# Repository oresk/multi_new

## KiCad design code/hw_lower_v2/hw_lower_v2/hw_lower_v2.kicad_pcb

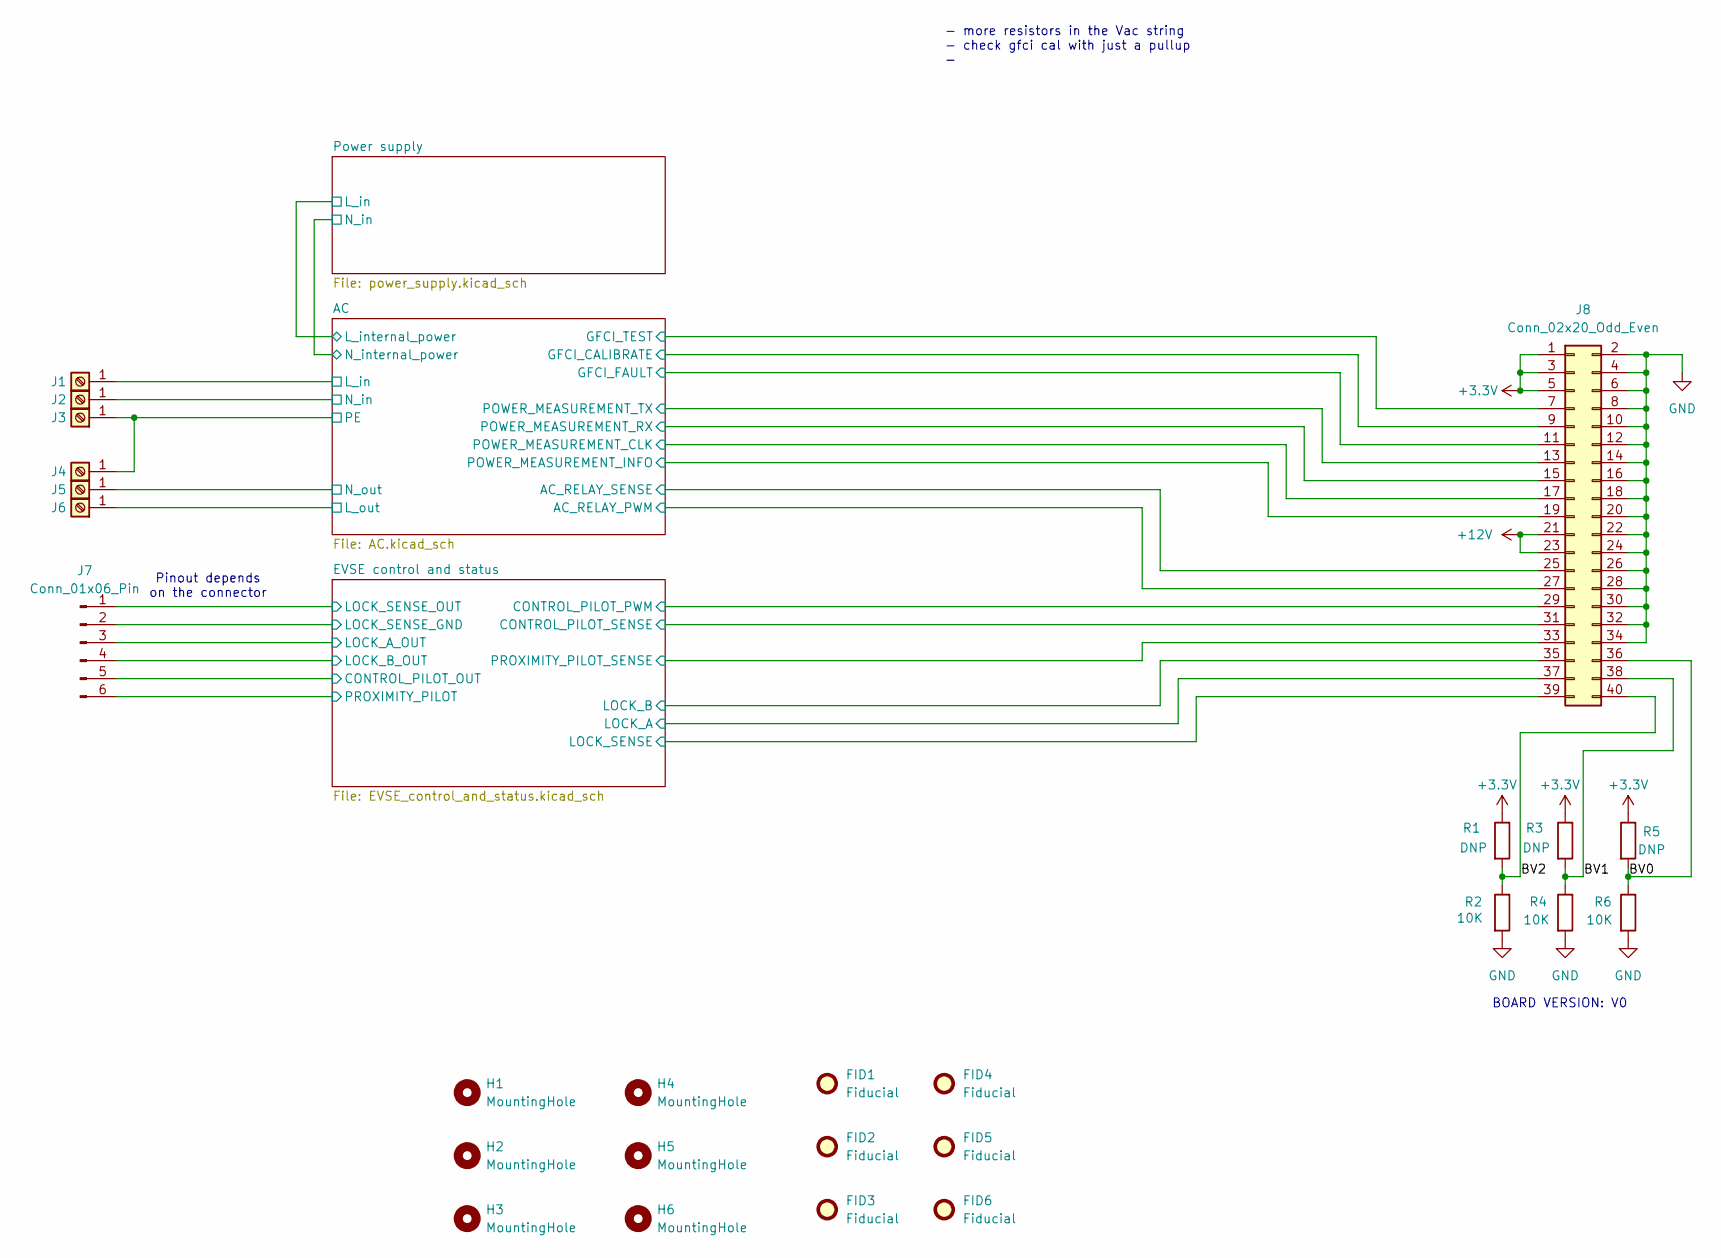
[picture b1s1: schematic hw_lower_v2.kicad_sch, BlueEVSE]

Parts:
FID1, FID2, FID3, FID4, FID5, FID6: Fiducial; Fiducial_1mm_Mask3mm
H1, H2: MountingHole; MountingHole_3.2mm_M3
H3, H4, H5, H6: MountingHole; MountingHole_3.2mm_M3_Pad
J1, J2, J3, J4, J5, J6: Screw_Terminal_01x01; CONN-TH_T44001; LCSC C481447
J7: Conn_01x06_Pin; PinHeader_1x06_P2.54mm_Horizontal; LCSC C56816
J8: Conn_02x20_Odd_Even; PinHeader_2x20_P2.54mm_Vertical
R1, R3, R5: DNP; R_0603_1608Metric
R2, R4, R6: 10K; R_0603_1608Metric; LCSC C25804

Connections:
+12V: J8.21, J8.23; also elsewhere on the board
/AC/AC_RELAY_PWM: J8.27; also elsewhere on the board
/AC/AC_RELAY_SENSE: J8.25; also elsewhere on the board
/AC/GFCI_CALIBRATE: J8.9; also elsewhere on the board
/AC/GFCI_FAULT: J8.11; also elsewhere on the board
/AC/GFCI_TEST: J8.7; also elsewhere on the board
/AC/L_in: J1.1; also elsewhere on the board
/AC/L_out: J6.1; also elsewhere on the board
/AC/N_in: J2.1; also elsewhere on the board
/AC/N_out: J5.1; also elsewhere on the board
/AC/POWER_MEASUREMENT_CLK: J8.17; also elsewhere on the board
/AC/POWER_MEASUREMENT_INFO: J8.19; also elsewhere on the board
/AC/POWER_MEASUREMENT_RX: J8.15; also elsewhere on the board
/AC/POWER_MEASUREMENT_TX: J8.13; also elsewhere on the board
/BV0: J8.36, R5.2, R6.1
/BV1: J8.38, R3.2, R4.1
/BV2: J8.40, R1.2, R2.1
/EVSE control and status/CONTROL_PILOT_OUT: J7.5; also elsewhere on the board
/EVSE control and status/CONTROL_PILOT_PWM: J8.29; also elsewhere on the board
/EVSE control and status/CONTROL_PILOT_SENSE: J8.31; also elsewhere on the board
/EVSE control and status/LOCK_A: J8.37; also elsewhere on the board
/EVSE control and status/LOCK_A_OUT: J7.3; also elsewhere on the board
/EVSE control and status/LOCK_B: J8.35; also elsewhere on the board
/EVSE control and status/LOCK_B_OUT: J7.4; also elsewhere on the board
/EVSE control and status/LOCK_SENSE: J7.1, J8.39; also elsewhere on the board
/EVSE control and status/PROXIMITY_PILOT: J7.6, J8.33; also elsewhere on the board
Earth_Protective: J3.1, J4.1

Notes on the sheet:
BOARD VERSION: V0
Pinout depends on the connector
- more resistors in the Vac string - check gfci cal with just a pullup -

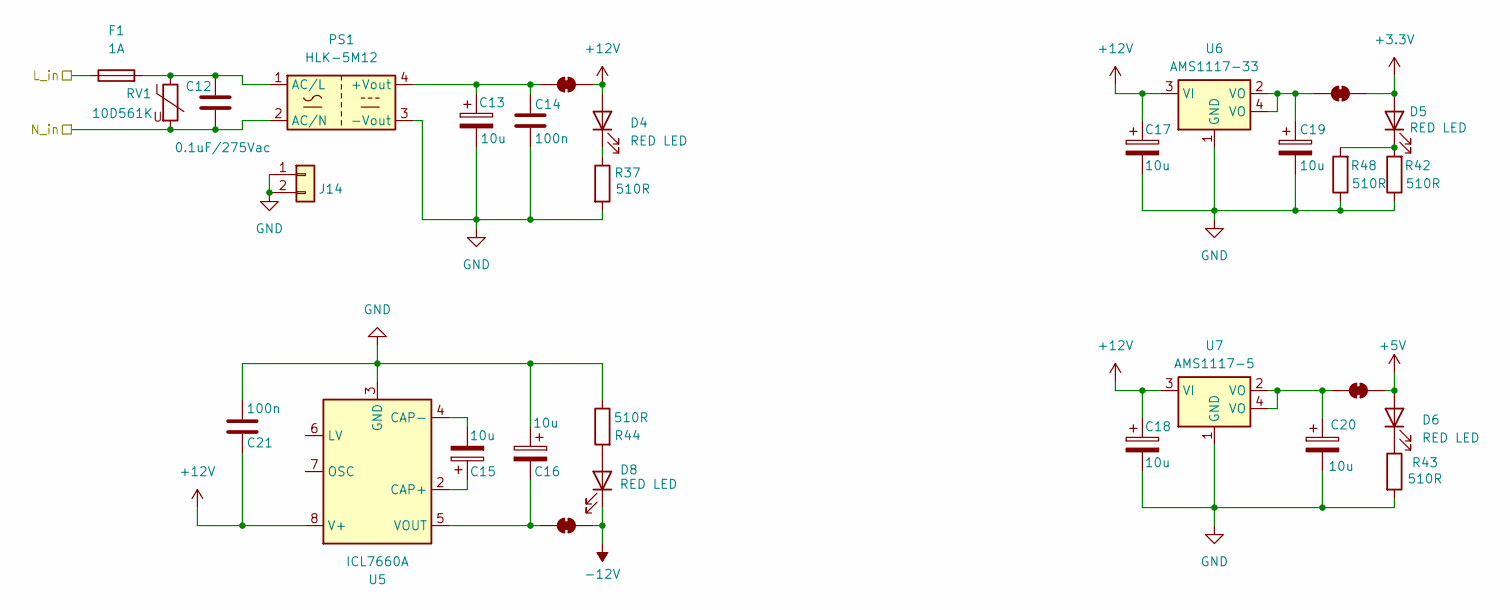
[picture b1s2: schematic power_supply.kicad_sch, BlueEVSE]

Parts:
C12: 0.1uF/275Vac; CAP-TH_L13.0-W6.0-P10.00-D0.6; LCSC C489079
C13, C15, C16, C17, C18, C19, C20: 10u; CP_Elec_4x5.4; LCSC C86602
C14, C21: 100n; C_0805_2012Metric; LCSC C327162
D4, D5, D6, D8: RED LED; D_0603_1608Metric; LCSC C7496820
F1: 1A; F1206; LCSC C910830
J14: Conn_01x02; PinHeader_1x02_P2.54mm_Vertical
JP1, JP3, JP4, JP5: SolderJumper_2_Bridged; SolderJumper-2_P1.3mm_Bridged2Bar_RoundedPad1.0x1.5mm
PS1: HLK-5M12; Converter_ACDC_Hi-Link_HLK-5Mxx; LCSC C209908
R37, R42, R43, R44, R48: 510R; R_0603_1608Metric; LCSC C23193
RV1: 10D561K; RES-TH_L12.5-W4.4-P7.50-D0.8-S3.60; LCSC C2761663
U5: ICL7660A; SOIC-8_L5.0-W4.0-P1.27-LS6.0-BL; LCSC C7881
U6: AMS1117-33; SOT-223_L6.7-W3.5-P2.30-BR; LCSC C6186
U7: AMS1117-5; SOT-223_L6.7-W3.5-P2.30-BR; LCSC C6187

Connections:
+12V: C17.1, C18.1, C21.1, D4.2 (A), JP1.1 (A), U5.8 (V+), U6.3 (VI), U7.3 (VI); also elsewhere on the board
/AC/L_internal_power: F1.1; also elsewhere on the board
/AC/N_internal_power: C12.2, PS1.2 (AC/N), RV1.2; also elsewhere on the board
unnamed: D4.1 (K), R37.1
unnamed: D5.1 (K), R42.2, R48.2
unnamed: D6.1 (K), R43.1
unnamed: D8.2 (A), R44.2
unnamed: C13.1, C14.1, JP1.2 (B), PS1.4 (+Vout)
unnamed: C16.2, JP3.2 (B), U5.5 (VOUT)
unnamed: C19.1, JP4.2 (B), U6.2 (VO), U6.4 (VO)
unnamed: C20.1, JP5.2 (B), U7.2 (VO), U7.4 (VO)
unnamed: C12.1, F1.2, PS1.1 (AC/L), RV1.1
unnamed: C15.1, U5.2 (CAP+)
unnamed: C15.2, U5.4 (CAP-)

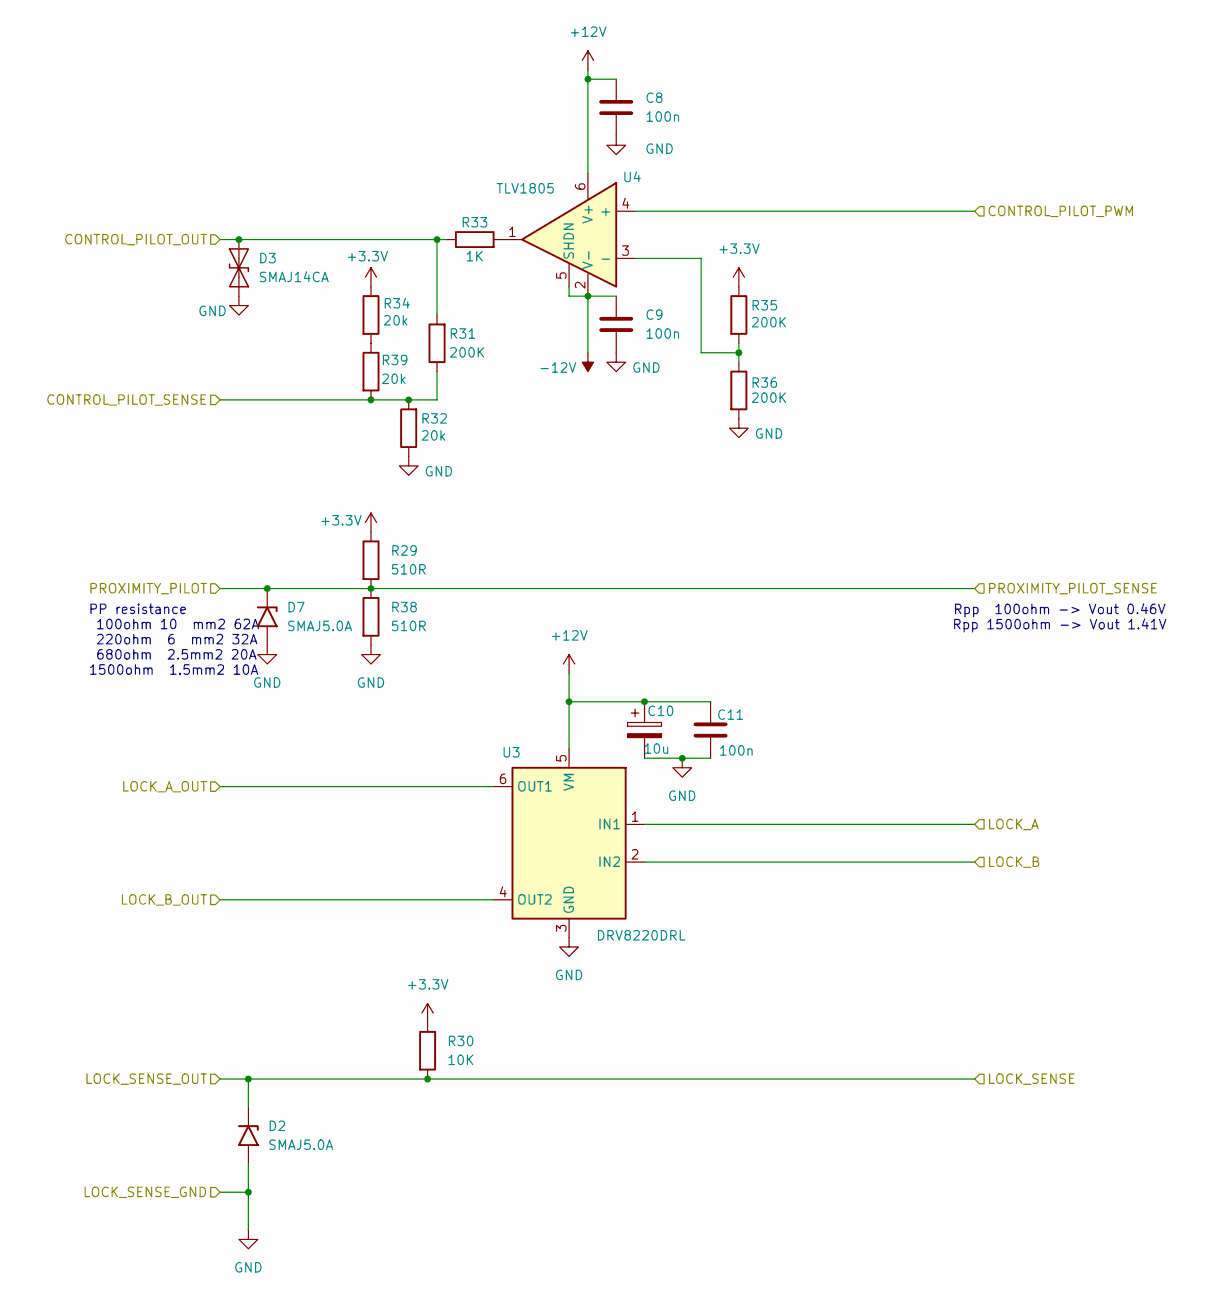
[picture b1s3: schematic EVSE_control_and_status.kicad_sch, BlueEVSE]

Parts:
C8, C9, C11: 100n; C_0805_2012Metric; LCSC C327162
C10: 10u; CP_Elec_4x5.4; LCSC C86602
D2, D7: SMAJ5.0A; D_SMA; LCSC C7473307
D3: SMAJ14CA; D_SMA; LCSC C908820
R29, R38: 510R; R_0603_1608Metric; LCSC C23193
R30: 10K; R_0603_1608Metric; LCSC C25804
R31, R35, R36: 200K; R_0603_1608Metric; LCSC C2989567
R32, R34, R39: 20k; R_0603_1608Metric
R33: 1K; R_0603_1608Metric
U3: DRV8220DRL; SOT-563; LCSC C3681351
U4: TLV1805; SOT-23-6_L2.9-W1.6-P0.95-LS2.8-BR; LCSC C2862164

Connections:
+12V: C8.1, C10.1, C11.1, U3.5 (VM), U4.6 (V+); also elsewhere on the board
/EVSE control and status/CONTROL_PILOT_OUT: D3.2 (A2), R31.2, R33.1; also elsewhere on the board
/EVSE control and status/CONTROL_PILOT_PWM: U4.4 (+); also elsewhere on the board
/EVSE control and status/CONTROL_PILOT_SENSE: R31.1, R32.2, R39.2; also elsewhere on the board
/EVSE control and status/LOCK_A: U3.1 (IN1); also elsewhere on the board
/EVSE control and status/LOCK_A_OUT: U3.6 (OUT1); also elsewhere on the board
/EVSE control and status/LOCK_B: U3.2 (IN2); also elsewhere on the board
/EVSE control and status/LOCK_B_OUT: U3.4 (OUT2); also elsewhere on the board
/EVSE control and status/LOCK_SENSE: D2.1 (A1), R30.2; also elsewhere on the board
/EVSE control and status/PROXIMITY_PILOT: D7.1 (A1), R29.2, R38.1; also elsewhere on the board
unnamed: R33.2, U4.1
unnamed: R34.2, R39.1
unnamed: R35.2, R36.1, U4.3 (-)

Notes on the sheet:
PP resistance 100ohm 10 mm2 62A 220ohm 6 mm2 32A 680ohm 2.5mm2 20A 1500ohm 1.5mm2 10A
Rpp 100ohm -> Vout 0.46V Rpp 1500ohm -> Vout 1.41V

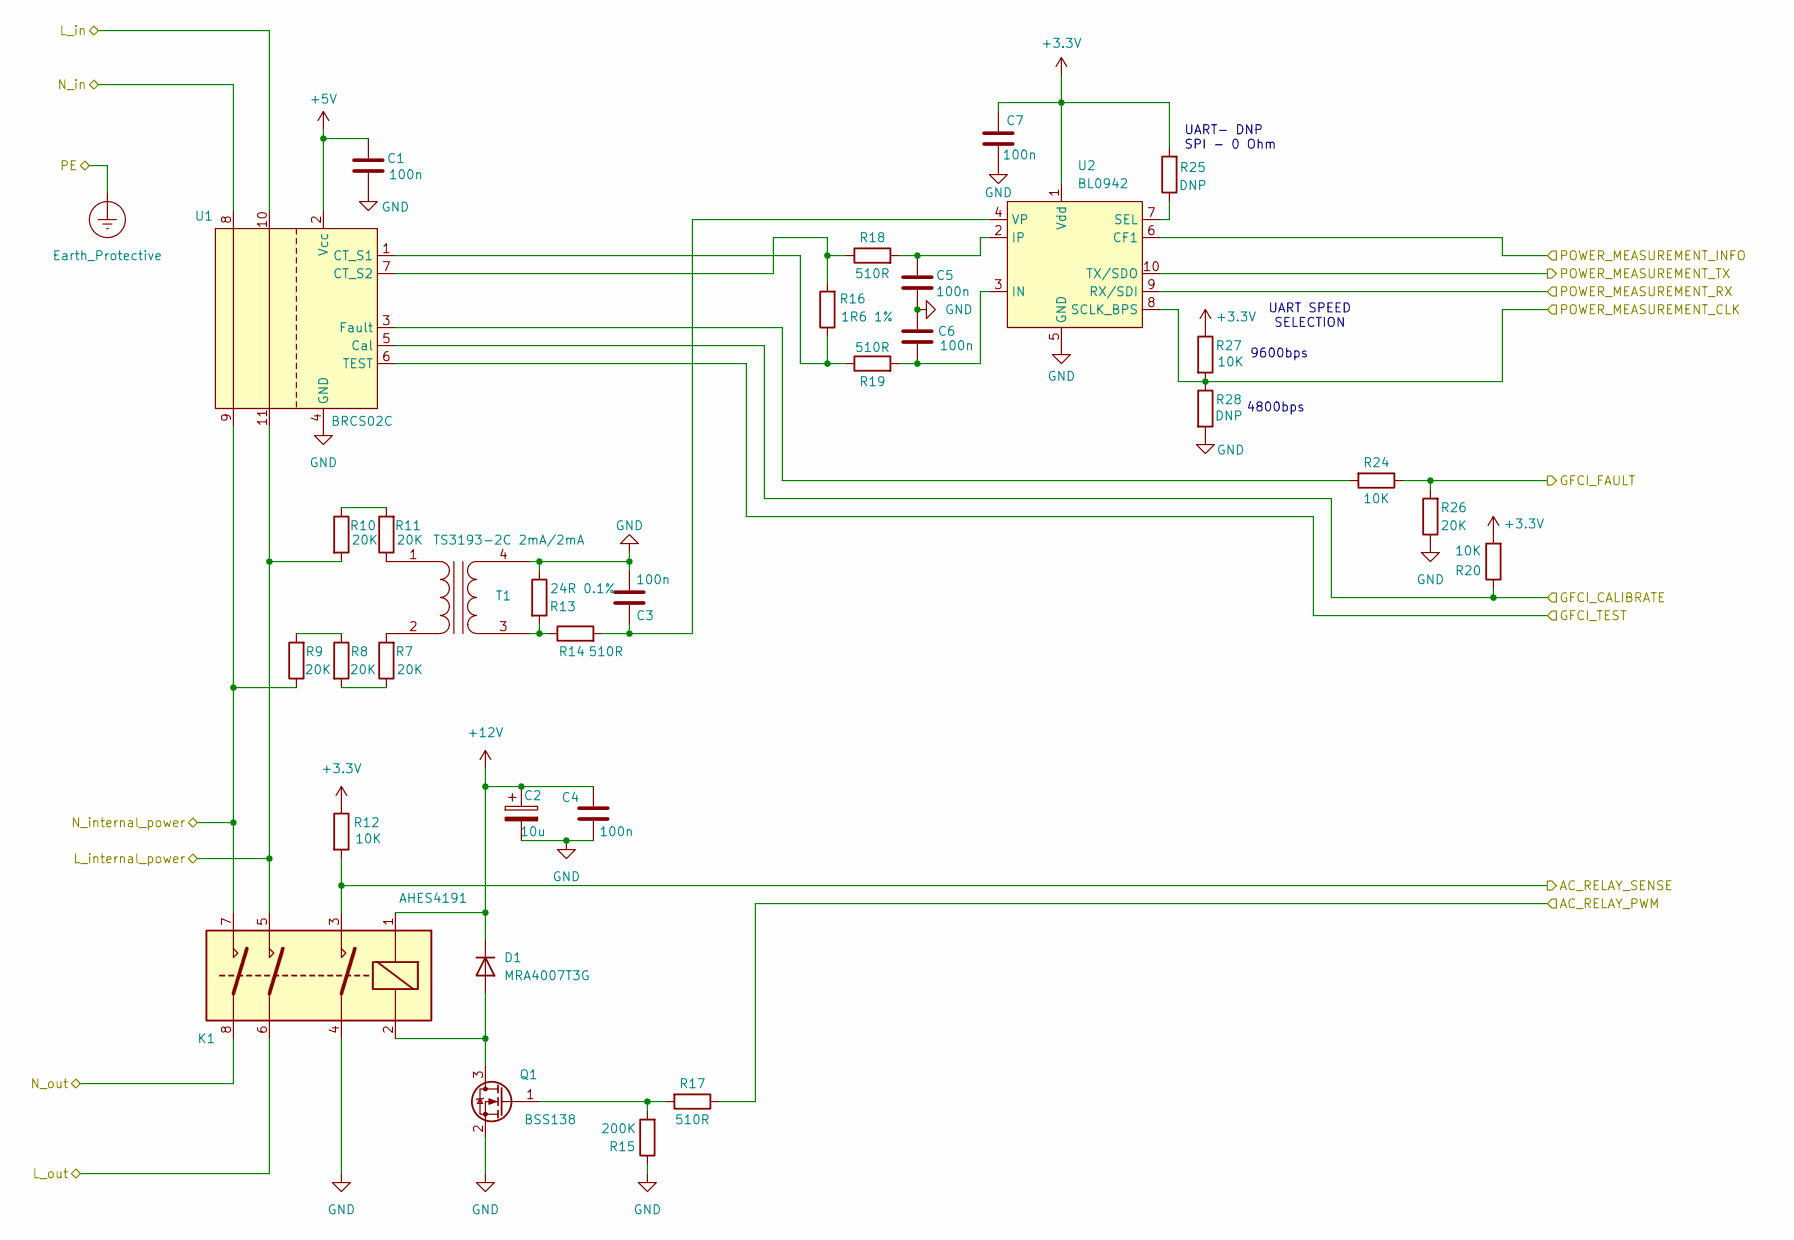
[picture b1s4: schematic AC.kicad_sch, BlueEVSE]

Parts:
C1, C3, C4, C5, C6, C7: 100n; C_0805_2012Metric; LCSC C327162
C2: 10u; CP_Elec_4x5.4; LCSC C86602
D1: MRA4007T3G; D_SMA; LCSC C47921
K1: AHES4191; panasonic HE-s; LCSC C719192
Q1: BSS138; SOT-23; LCSC C112239
R7, R8, R9, R10, R11, R26: 20K; R_1206_3216Metric; LCSC C706407
R12, R20, R24, R27: 10K; R_0603_1608Metric; LCSC C25804
R13: 24R 0.1%; R_0603_1608Metric; LCSC C317933
R14, R17, R18, R19: 510R; R_0603_1608Metric; LCSC C23193
R15: 200K; R_0603_1608Metric; LCSC C2989567
R16: 1R6 1%; R_0603_1608Metric; LCSC C365113
R25, R28: DNP; R_0603_1608Metric
T1: TS3193-2C 2mA/2mA; TS3193-2C; LCSC C2896606
U1: BRCS02C; BRCS02C_2
U2: BL0942; SSOP-10_L4.9-W3.9-P1.00-LS6.0-BL; LCSC C2837510

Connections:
+12V: C2.1, C4.1, D1.1 (K), K1.1; also elsewhere on the board
/AC/AC_RELAY_PWM: R17.1; also elsewhere on the board
/AC/AC_RELAY_SENSE: K1.3, R12.2; also elsewhere on the board
/AC/GFCI_FAULT: R24.1, R26.2; also elsewhere on the board
/AC/L_in: U1.10; also elsewhere on the board
/AC/L_internal_power: K1.5, R10.2, U1.11; also elsewhere on the board
/AC/L_out: K1.6; also elsewhere on the board
/AC/N_in: U1.8; also elsewhere on the board
/AC/N_internal_power: K1.7, R9.1, U1.9; also elsewhere on the board
/AC/N_out: K1.8; also elsewhere on the board
/AC/POWER_MEASUREMENT_CLK: R27.2, R28.1, U2.8 (SCLK_BPS); also elsewhere on the board
/AC/POWER_MEASUREMENT_INFO: U2.6 (CF1); also elsewhere on the board
/AC/POWER_MEASUREMENT_RX: U2.9 (RX/SDI); also elsewhere on the board
/AC/POWER_MEASUREMENT_TX: U2.10 (TX/SDO); also elsewhere on the board
unnamed: D1.2 (A), K1.2, Q1.3 (D)
unnamed: Q1.1 (G), R15.2, R17.2
unnamed 40: R20.1, U1.5 (Cal); also elsewhere on the board
unnamed 41: U1.6 (TEST); also elsewhere on the board
unnamed 42: R7.1, R8.2; also elsewhere on the board
unnamed 43: R8.1, R9.2; also elsewhere on the board
unnamed 44: R10.1, R11.2; also elsewhere on the board
unnamed 47: R11.1, T1.1 (AA); also elsewhere on the board
unnamed 48: R7.2, T1.2 (AB); also elsewhere on the board
unnamed: R13.2, R14.1, T1.3 (SA)
unnamed: R16.1, R19.1, U1.1 (CT_S1)
unnamed: R16.2, R18.1, U1.7 (CT_S2)
unnamed: R24.2, U1.3 (Fault)
unnamed: C6.2, R19.2, U2.3 (IN)
unnamed: C5.1, R18.2, U2.2 (IP)
unnamed: R25.1, U2.7 (SEL)
unnamed: C3.1, R14.2, U2.4 (VP)

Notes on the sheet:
4800bps
UART SPEED SELECTION
UART- DNP SPI - 0 Ohm
9600bps

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
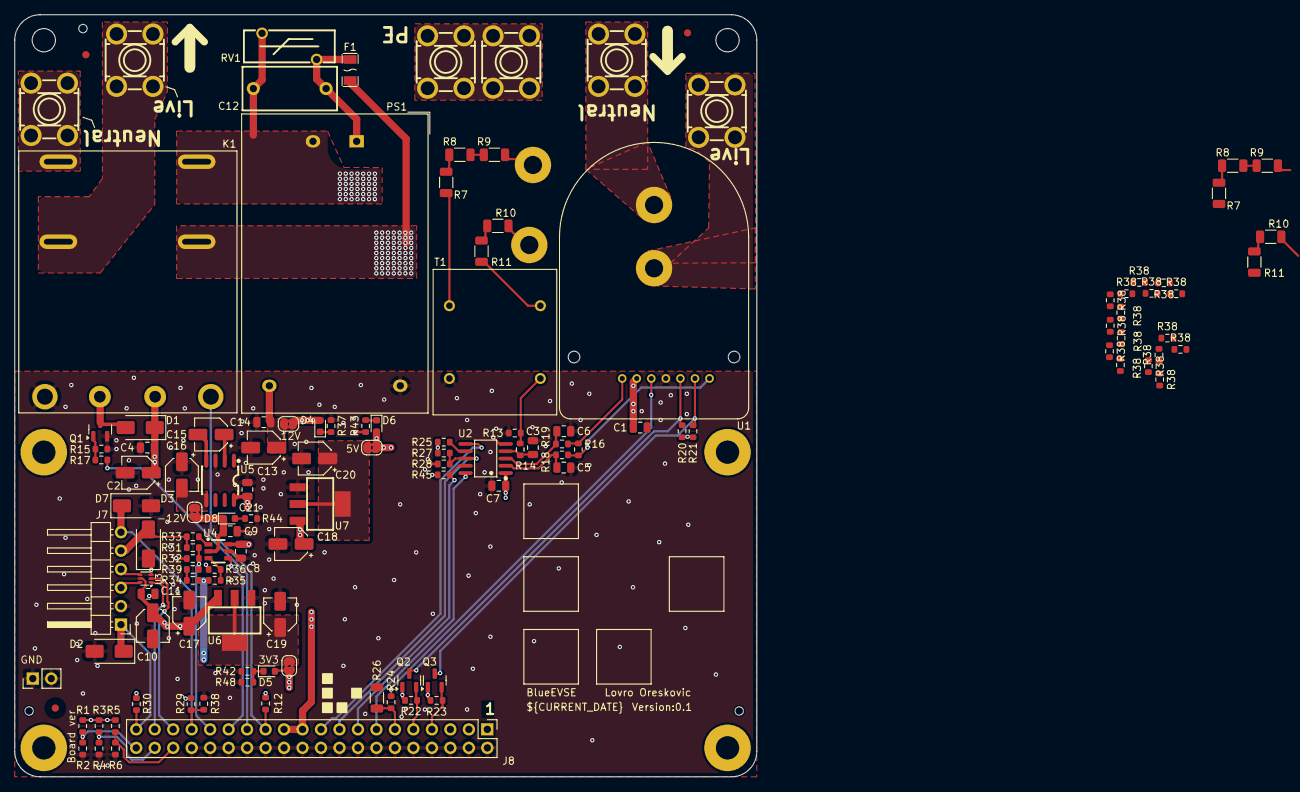
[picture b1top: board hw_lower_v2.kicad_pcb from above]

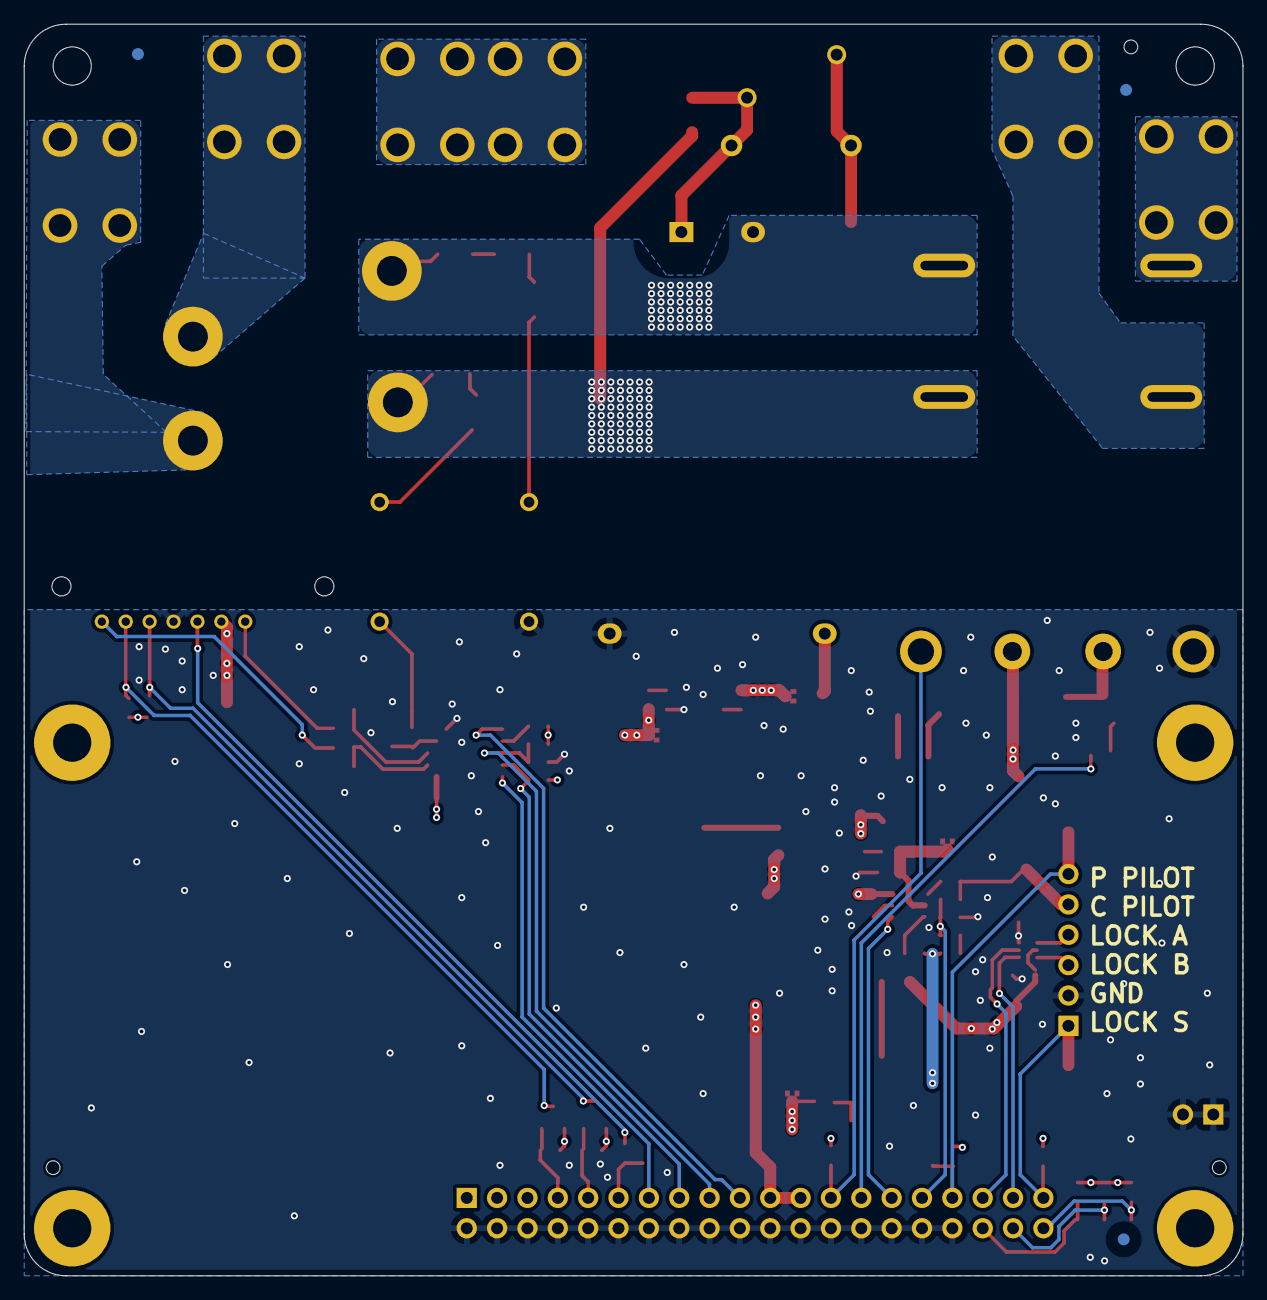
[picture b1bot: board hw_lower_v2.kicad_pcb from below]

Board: 4 copper layers, 102.0 x 104.8 mm, 134 parts (3 on the bottom side), 64 nets.

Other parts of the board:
Q2, Q3: BSS138; SOT-23
R7#2, R8#2, R9#2, R10#2, R11#2: 20K; R_1206_3216Metric
R21, R22, R23, R45: 10K; R_0603_1608Metric
R38#2, R38#3, R38#4, R38#5, R38#6, R38#7, R38#8, R38#9, R38#10, R38#11, R38#12, R38#13, R38#14, R38#15, R38#16, R38#17: 510R; R_0603_1608Metric

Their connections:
/AC/GFCI_CALIBRATE: Q2.2 (S), R22.1; also elsewhere on the board
/AC/GFCI_TEST: Q3.2 (S), R23.1; also elsewhere on the board
/AC/L_internal_power: R10#2.2; also elsewhere on the board
/AC/N_internal_power: R9#2.1; also elsewhere on the board
/AC/POWER_MEASUREMENT_RX: R45.2; also elsewhere on the board
/EVSE control and status/PROXIMITY_PILOT: R38#14.1; also elsewhere on the board
unnamed 40: Q2.3 (D); also elsewhere on the board
unnamed 41: Q3.3 (D), R21.1; also elsewhere on the board
unnamed 42: R7#2.1, R8#2.2; also elsewhere on the board
unnamed 43: R8#2.1, R9#2.2; also elsewhere on the board
unnamed 44: R10#2.1, R11#2.2; also elsewhere on the board
unnamed 47: R11#2.1; also elsewhere on the board
unnamed 48: R7#2.2; also elsewhere on the board

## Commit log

2024-05-23 initial commit with a bunch of notes
2024-06-01 general outline of the lower board schematic
2024-06-01 add kicad gitignore
2024-06-01 add .gitignore for kicad
2024-06-01 misc
2024-07-14 started full lower pcb version
2024-07-17 hierarcyhal sheets
2024-07-18 further lower board sch work
2024-07-20 add 12V voltage inverter and polish
2024-07-22 schematic is done
2024-07-22 update todone
2024-07-23 finishing up sch and creating footprints
2024-07-25 finished schematic, started first pass of layout
2024-07-25 Preliminary pcb component placement done
    PCB size currently is around 100mm X 100mm with the mezanine board being ~40mm x 100mm
2024-07-25 new notes
2024-07-28 grouped and positioned components
2024-07-28 further placement and pin relocation
2024-07-28 commit before experimenting
2024-07-28 add components
2024-07-29 switch power pin headers for jumpers
2024-07-29 have one project part library
2024-07-29 add kicad lock files to git ignore
2024-07-29 right before tracks
2024-07-30 routed most of the board
2024-08-06 before the final route
2024-08-06 layout 99% finished
2024-08-07 finish 3d models
2024-08-07 moved stuff around a little bit, will optimise the number of components now
2024-08-08 simplify component values
2024-08-08 made a full reposition of the whole pcb. When I get everything working, the milkv module can be on the bottom pcb and all the device specific devices can be on the other pcb. Also now conceptualy, th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
2024-08-09 Relalaid out the LV part of the board.
    One or two small things left to do.
    Prepared for the 2.0 version of the PCB where the duo01 module can be
    put on the lower board.
    Also it is possible to make a sandwitch situation, and make a long thin
    product.
2024-08-09 almost ready :-)
2024-08-09 add JLCPCB tooling holes and simplify further
2024-08-15 clean up old files
2024-08-15 write up decision on which os-es to use
2024-08-26 add notes about next steps
2024-10-03 wip zephyr
